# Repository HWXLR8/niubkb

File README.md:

# 牛逼KB
An ergonomic ortholinear keyboard inspired by the Atrues.

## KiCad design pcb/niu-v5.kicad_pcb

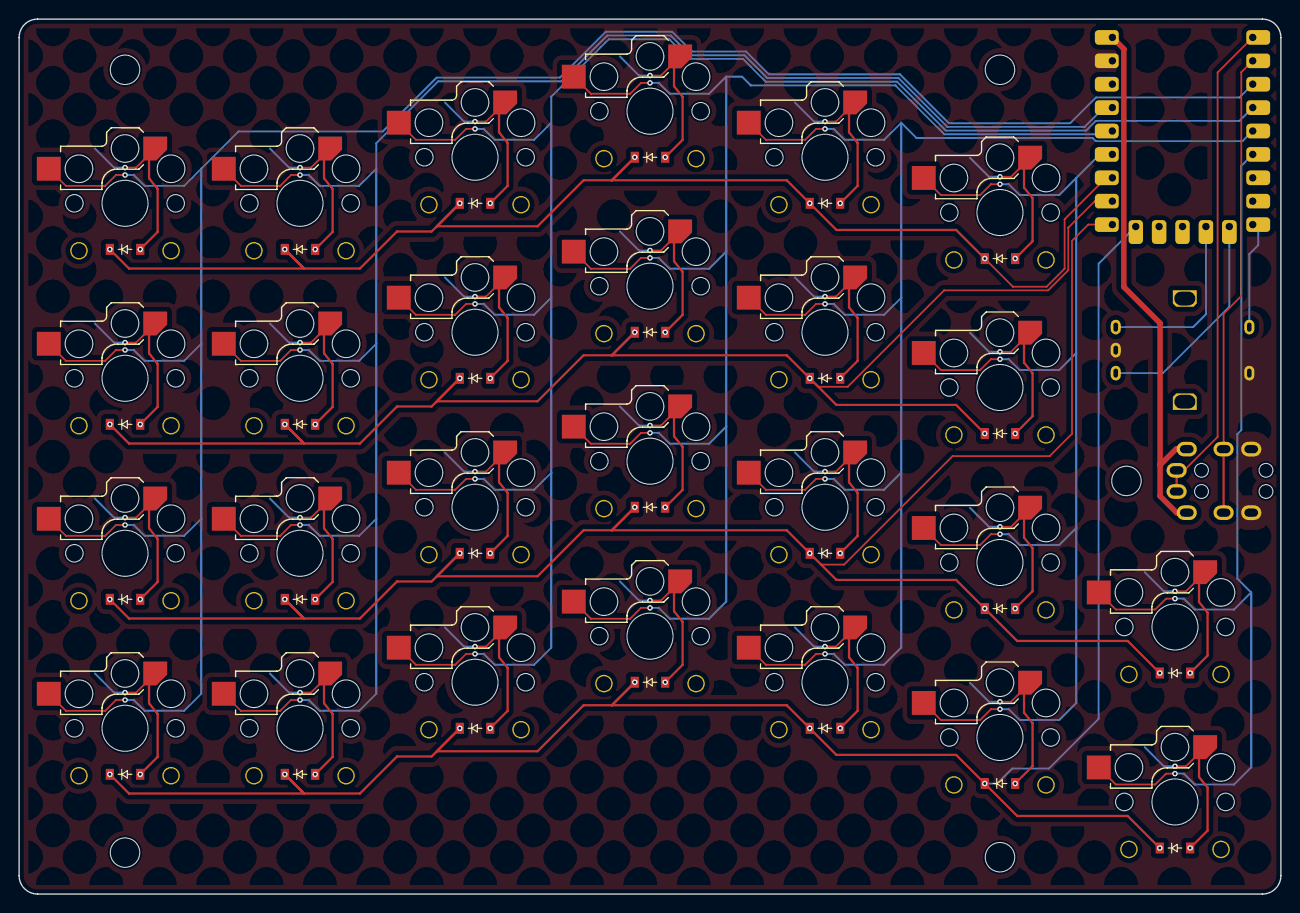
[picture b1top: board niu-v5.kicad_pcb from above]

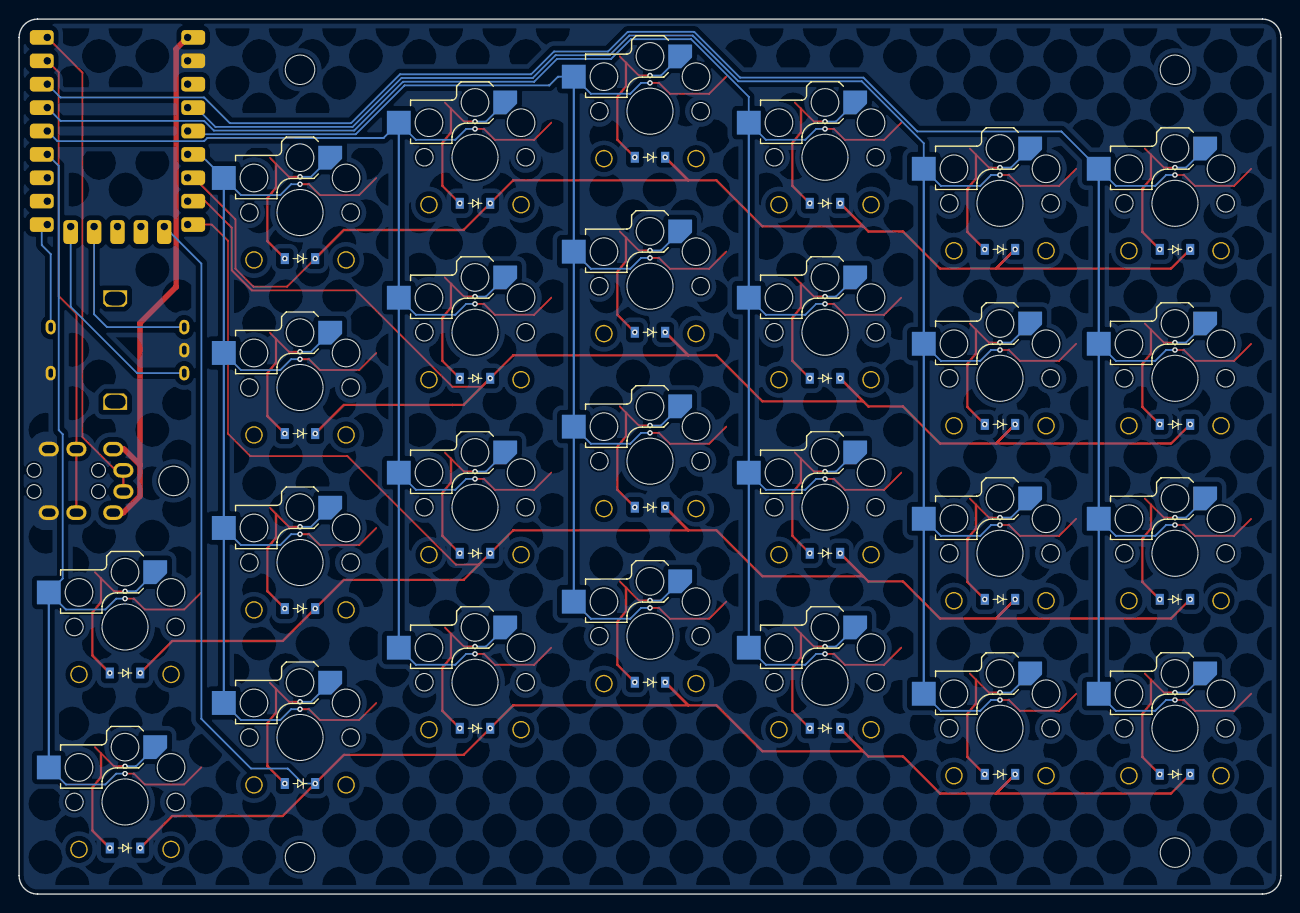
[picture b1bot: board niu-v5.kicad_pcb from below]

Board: 2 copper layers, 137.0 x 95.0 mm, 60 parts (26 on the bottom side), 44 nets.

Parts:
D1, D2, D3, D4, D5, D6, D7, D8, D9, D10, D11, D12, D13, D14, D15, D16, D17, D18, D19, D20, D21, D22, D23, D24, D25, D26: diode_tht_sod123
MCU1: mcu_rp2040_zero
MH1, MH2, MH3, MH4, MH5: mounting_hole_npth
RE1: rotary_encoder_ec11_ec12
S1, S2, S3, S4, S5, S6, S7, S8, S9, S10, S11, S12, S13, S14, S15, S16, S17, S18, S19, S20, S21, S22, S23, S24, S25, S26: switch_choc_v1_v2
TRRS1: trrs_pj320a (reversible)

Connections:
5V: MCU1.1, TRRS1.4
ENC_A: MCU1.14, RE1.A
ENC_B: MCU1.13, RE1.C
ENC_SW: MCU1.15, RE1.S1
GND: MCU1.2, RE1.B, RE1.S2, TRRS1.2
P4: MCU1.4, S5.2, S6.2, S7.2, S8.2
P5: MCU1.5, S13.2, S14.2, S15.2, S16.2
P6: MCU1.6, S21.2, S22.2, S23.2, S24.2
P7: D4.1, D8.1, D12.1, D16.1, D20.1, D24.1, MCU1.7
P8: D3.1, D7.1, D11.1, D15.1, D19.1, D23.1, MCU1.8
P9: D2.1, D6.1, D10.1, D14.1, D18.1, D22.1, D26.1, MCU1.9
P10: D1.1, D5.1, D9.1, D13.1, D17.1, D21.1, D25.1, MCU1.10
P18: MCU1.18, S25.2, S26.2
P19: MCU1.19, S17.2, S18.2, S19.2, S20.2
P20: MCU1.20, S9.2, S10.2, S11.2, S12.2
P21: MCU1.21, S1.2, S2.2, S3.2, S4.2
RX: MCU1.22, TRRS1.3
TX: MCU1.23, TRRS1.5
index_bottom: D17.2, S17.1
index_home: D19.2, S19.1
index_lower: D18.2, S18.1
index_top: D20.2, S20.1
inner_bottom: D21.2, S21.1
inner_home: D23.2, S23.1
inner_lower: D22.2, S22.1
inner_top: D24.2, S24.1
middle_bottom: D13.2, S13.1
middle_home: D15.2, S15.1
middle_lower: D14.2, S14.1
middle_top: D16.2, S16.1
outer_bottom: D1.2, S1.1
outer_home: D3.2, S3.1
outer_lower: D2.2, S2.1
outer_top: D4.2, S4.1
pinky_bottom: D5.2, S5.1
pinky_home: D7.2, S7.1
pinky_lower: D6.2, S6.1
pinky_top: D8.2, S8.1
ring_bottom: D9.2, S9.1
ring_home: D11.2, S11.1
ring_lower: D10.2, S10.1
ring_top: D12.2, S12.1
thumb_bottom: D25.2, S25.1
thumb_lower: D26.2, S26.1

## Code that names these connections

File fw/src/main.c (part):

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#define LINK_SM   0

// EC11 on the right half. MCU pads 14/13/15 -> GP9/GP10/GP8 (ENC_A/ENC_B/ENC_SW).
#define ENC_A_PIN  9
#define ENC_B_PIN  10
#define ENC_SW_PIN 8

//// HANDEDNESS

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#else

static void link_init(void) {
    gpio_init(ENC_A_PIN);
    gpio_set_dir(ENC_A_PIN, GPIO_IN);
    gpio_pull_up(ENC_A_PIN);
    gpio_init(ENC_B_PIN);
    gpio_set_dir(ENC_B_PIN, GPIO_IN);
    gpio_pull_up(ENC_B_PIN);
    gpio_init(ENC_SW_PIN);
    gpio_set_dir(ENC_SW_PIN, GPIO_IN);
    gpio_pull_up(ENC_SW_PIN);

    uint offset = pio_add_program(LINK_PIO, &uart_tx_program);
    uart_tx_program_init(LINK_PIO, LINK_SM, offset, LINK_PIN, LINK_BAUD);
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    static uint8_t prev_state = 0;
    static int position = 0, last_direction = 0;

    uint8_t a = gpio_get(ENC_A_PIN) ? 1 : 0;
    uint8_t b = gpio_get(ENC_B_PIN) ? 1 : 0;
    uint8_t cur_state = (a << 1) | b;
    if (cur_state == prev_state) return 0;

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// One pulse per press of the shaft, active low.
static bool encoder_sw_task(void) {
    static bool prev = false;
    bool now = !gpio_get(ENC_SW_PIN);
    bool pressed = now && !prev;
    prev = now;
    return pressed;
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
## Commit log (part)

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2023-02-19 init
2023-02-19 rename niubkb.yaml -> niu.yaml
2023-02-20 Add trrs. Change some units from cx/cy to default units. Adjust tab spacing to make room for mounting posts.
2023-02-23 add some mounting holes
2023-02-23 un-rotate footprints
2023-02-23 align mcu and trrs jack
2023-02-23 tentative tab+hole placement complete
2023-02-28 add routed pcb and silkscreen footprint library
2023-03-15 add tab to remove jagged section under row 5
2023-04-13 add skeleton fw
2023-04-14 full layout working for left half
2023-11-19 add .gitignore
2023-11-19 change bin path to work with global bin
2023-11-19 add merged version
2023-11-19 rename niu -> niu-split
2023-11-26 remove tabs/holes in yaml in favor of manual placement in kicad
2024-01-14 add routed merged pcb
2024-01-14 fix hole sizes
2024-01-14 finalize merged pcb
2024-01-14 remove silkscreen on promicro
2024-01-14 rename niu_routed -> niu_split
2024-01-14 move pcbs to separate dir
2024-01-14 add pcb pics
2024-01-14 add README
2024-01-14 fix image widths
2024-01-14 update gitignore
2024-01-14 add LICENSE
2024-01-31 add case (WIP)
2024-01-31 add script for generating mounting holes in openscad
2024-02-07 add case
2024-02-07 add kicad project files to gitignore
2024-02-08 rename niu-merged.yaml -> niu.yaml
2024-02-11 - move thumb key to bottom row net - change key tilt from 6 -> 7 - dos2unix
2024-02-11 add auto generated pcb outline
2024-02-11 center mcu
2024-02-11 lower mcu position
2024-02-11 add ergogen submodule
2024-02-11 change ergogen binary path to submodule dir
2024-02-13 add mounting holes
2024-02-13 lower mcu even further
2024-02-14 fix right hand column wiring
2024-02-14 update ergogen submodule
2024-02-14 change net names to use port numbers
2024-02-15 finalize v2
2024-02-15 update submodule
2024-02-15 remove split keyboard and associated footprints
2024-02-15 update pcb pics
2024-03-30 add m2 mounting holes, reduce outline size (WIP)
2024-03-31 Finalize V3 layout
    - drop pinky column stagger
    - rename rows
    - place all mounting holes
    - clean up board outline
    - add second thumb key
2024-04-09 route compact pcb
2024-05-13 [ERGOGEN] update submodule
2024-05-13 [PCB] Add silkscreen, change hatch fill to solid
2024-05-14 [DOC] Update PCB pics
2024-05-14 [DOC] Add missing PCB pic
2024-05-31 [FW] consolodate pins.h into Keyboard.h
2024-10-12 add jc pcb
2025-02-16 final ver
2025-02-16 [git] ignore backup files and gerbers
2025-02-16 [pcb] update naming scheme to use version numbers
2025-03-04 prototype v4
2025-04-27 finalize v4
2025-12-14 add niu-v5
2026-03-23 add rp2040 fw for v5
2026-03-24 add idle behaviour
2026-03-24 simplify idle logic
